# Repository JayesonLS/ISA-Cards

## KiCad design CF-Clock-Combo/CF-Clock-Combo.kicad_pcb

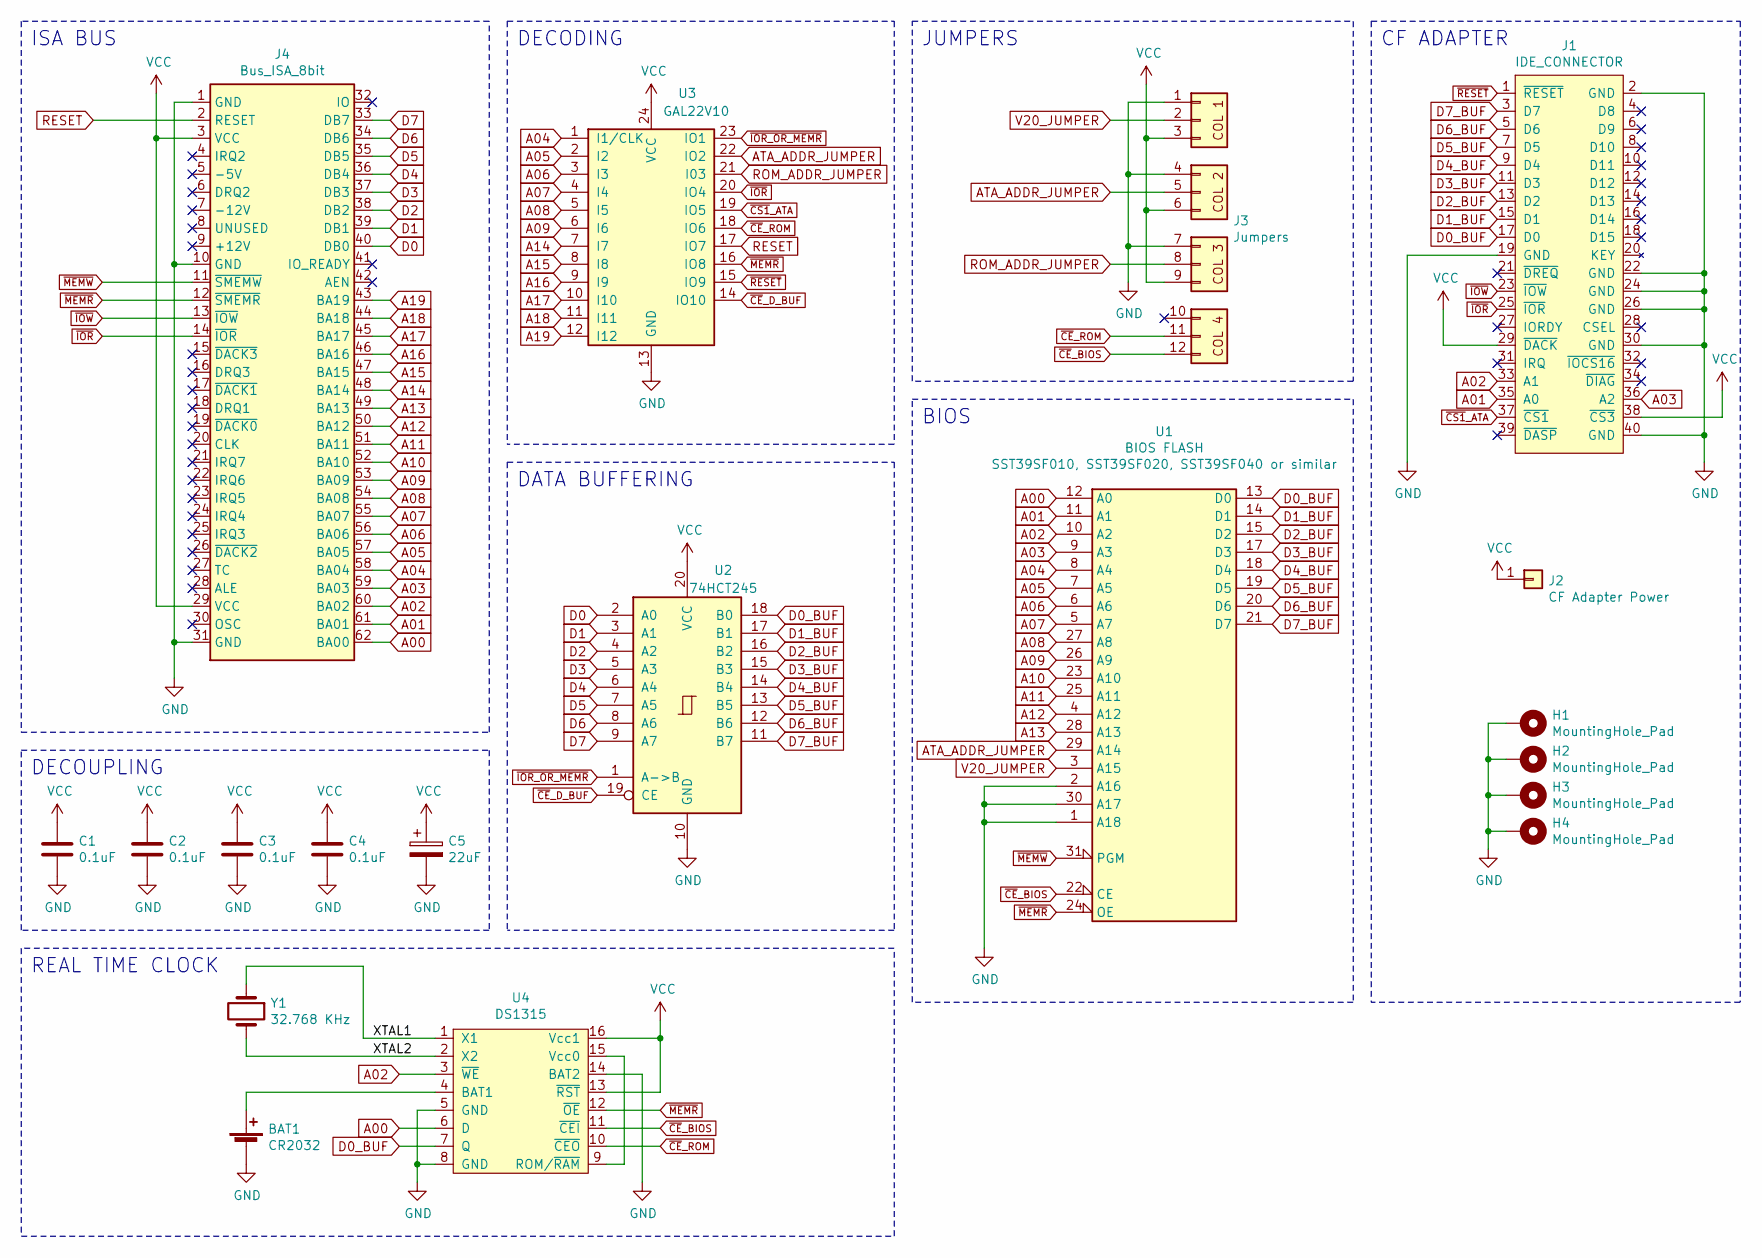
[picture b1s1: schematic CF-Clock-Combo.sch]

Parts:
BAT1: CR2032; BatteryHolder_Keystone_103_1x20mm
C1, C2, C3, C4: 0.1uF; C_Disc_D6.0mm_W2.5mm_P5.00mm
C5: 22uF; CP_Radial_D5.0mm_P2.50mm
H1, H2, H3, H4: MountingHole_Pad; MountingHole_3.5mm_Pad
J1: IDE_CONNECTOR; PinSocket_2x20_P2.54mm_Vertical
J2: CF Adapter Power; PinSocket_1x01_P2.54mm_Vertical
J3: Jumpers; PinHeader_3x04_P2.54mm_Vertical
J4: Bus_ISA_8bit; BUS_XT
U1: BIOS FLASH; DIP-32_W15.24mm_Socket
U2: 74HCT245; DIP-20_W7.62mm_Socket
U3: GAL22V10; DIP-24_W7.62mm_Socket
U4: DS1315; DIP-16_W7.62mm_Socket
Y1: 32.768 KHz; Crystal_C38-LF_D3.0mm_L8.0mm_Horizontal

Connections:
/XTAL1: U4.1 (X1), Y1.1
/XTAL2: U4.2 (X2), Y1.2
A00: J4.62 (BA00), U1.12 (A0), U4.6 (D)
A01: J1.35 (A0), J4.61 (BA01), U1.11 (A1)
A02: J1.33 (A1), J4.60 (BA02), U1.10 (A2), U4.3 (~WE)
A03: J1.36 (A2), J4.59 (BA03), U1.9 (A3)
A04: J4.58 (BA04), U1.8 (A4), U3.1 (I1/CLK)
A05: J4.57 (BA05), U1.7 (A5), U3.2 (I2)
A06: J4.56 (BA06), U1.6 (A6), U3.3 (I3)
A07: J4.55 (BA07), U1.5 (A7), U3.4 (I4)
A08: J4.54 (BA08), U1.27 (A8), U3.5 (I5)
A09: J4.53 (BA09), U1.26 (A9), U3.6 (I6)
A10: J4.52 (BA10), U1.23 (A10)
A11: J4.51 (BA11), U1.25 (A11)
A12: J4.50 (BA12), U1.4 (A12)
A13: J4.49 (BA13), U1.28 (A13)
A14: J4.48 (BA14), U3.7 (I7)
A15: J4.47 (BA15), U3.8 (I8)
A16: J4.46 (BA16), U3.9 (I9)
A17: J4.45 (BA17), U3.10 (I10)
A18: J4.44 (BA18), U3.11 (I11)
A19: J4.43 (BA19), U3.12 (I12)
ATA_ADDR_JUMPER: J3.5, U1.29 (A14), U3.22 (IO2)
D0: J4.40 (DB0), U2.2 (A0)
D0_BUF: J1.17 (D0), U1.13 (D0), U2.18 (B0), U4.7 (Q)
D1: J4.39 (DB1), U2.3 (A1)
D1_BUF: J1.15 (D1), U1.14 (D1), U2.17 (B1)
D2: J4.38 (DB2), U2.4 (A2)
D2_BUF: J1.13 (D2), U1.15 (D2), U2.16 (B2)
D3: J4.37 (DB3), U2.5 (A3)
D3_BUF: J1.11 (D3), U1.17 (D3), U2.15 (B3)
D4: J4.36 (DB4), U2.6 (A4)
D4_BUF: J1.9 (D4), U1.18 (D4), U2.14 (B4)
D5: J4.35 (DB5), U2.7 (A5)
D5_BUF: J1.7 (D5), U1.19 (D5), U2.13 (B5)
D6: J4.34 (DB6), U2.8 (A6)
D6_BUF: J1.5 (D6), U1.20 (D6), U2.12 (B6)
D7: J4.33 (DB7), U2.9 (A7)
D7_BUF: J1.3 (D7), U1.21 (D7), U2.11 (B7)
GND: BAT1.2 (-), C1.2, C2.2, C3.2, C4.2, C5.2, H1.1, H2.1, H3.1, H4.1, J1.2 (GND), J1.19 (GND), J1.22 (GND), J1.24 (GND), J1.26 (GND), J1.30 (GND), J1.40 (GND), J3.1, J3.4, J3.7, J4.1 (GND), J4.10 (GND), J4.31 (GND), U1.1 (A18), U1.2 (A16), U1.16 (GND), U1.30 (A17), U2.10 (GND), U3.13 (GND), U4.5 (GND), U4.8 (GND), U4.14 (BAT2)
unnamed: BAT1.1 (+), U4.4 (BAT1)
unnamed: U4.9 (ROM/~RAM), U4.15 (Vcc0)
RESET: J4.2 (RESET), U3.17 (IO7)
ROM_ADDR_JUMPER: J3.8, U3.21 (I03)
V20_JUMPER: J3.2, U1.3 (A15)
VCC: C1.1, C2.1, C3.1, C4.1, C5.1, J1.29 (~DACK), J1.38 (~CS3), J2.1, J3.3 (Pin_4), J3.6, J3.9, J4.3 (VCC), J4.29 (VCC), U1.32 (VCC), U2.20 (VCC), U3.24 (VCC), U4.13 (~RST), U4.16 (Vcc1)
~CE~_BIOS: J3.12, U1.22 (CE), U4.11 (~CEI)
~CE~_D_BUF: U2.19 (CE), U3.14 (IO10)
~CE~_ROM: J3.11, U3.18 (IO6), U4.10 (~CEO)
~CS1~_ATA: J1.37 (~CS1), U3.19 (IO5)
~IOR: J1.25 (~IOR), J4.14 (~IOR), U3.20 (IO4)
~IOR_OR_MEMR: U2.1 (A->B), U3.23 (IO1)
~IOW: J1.23 (~IOW), J4.13 (~IOW)
~MEMR: J4.12 (~SMEMR), U1.24 (OE), U3.16 (IO8), U4.12 (~OE)
~MEMW: J4.11 (~SMEMW), U1.31 (PGM)
~RESET: J1.1 (~RESET), U3.15 (IO9)

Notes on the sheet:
ISA BUS
DECOUPLING
DATA BUFFERING
DECODING
BIOS
CF ADAPTER
JUMPERS
REAL TIME CLOCK

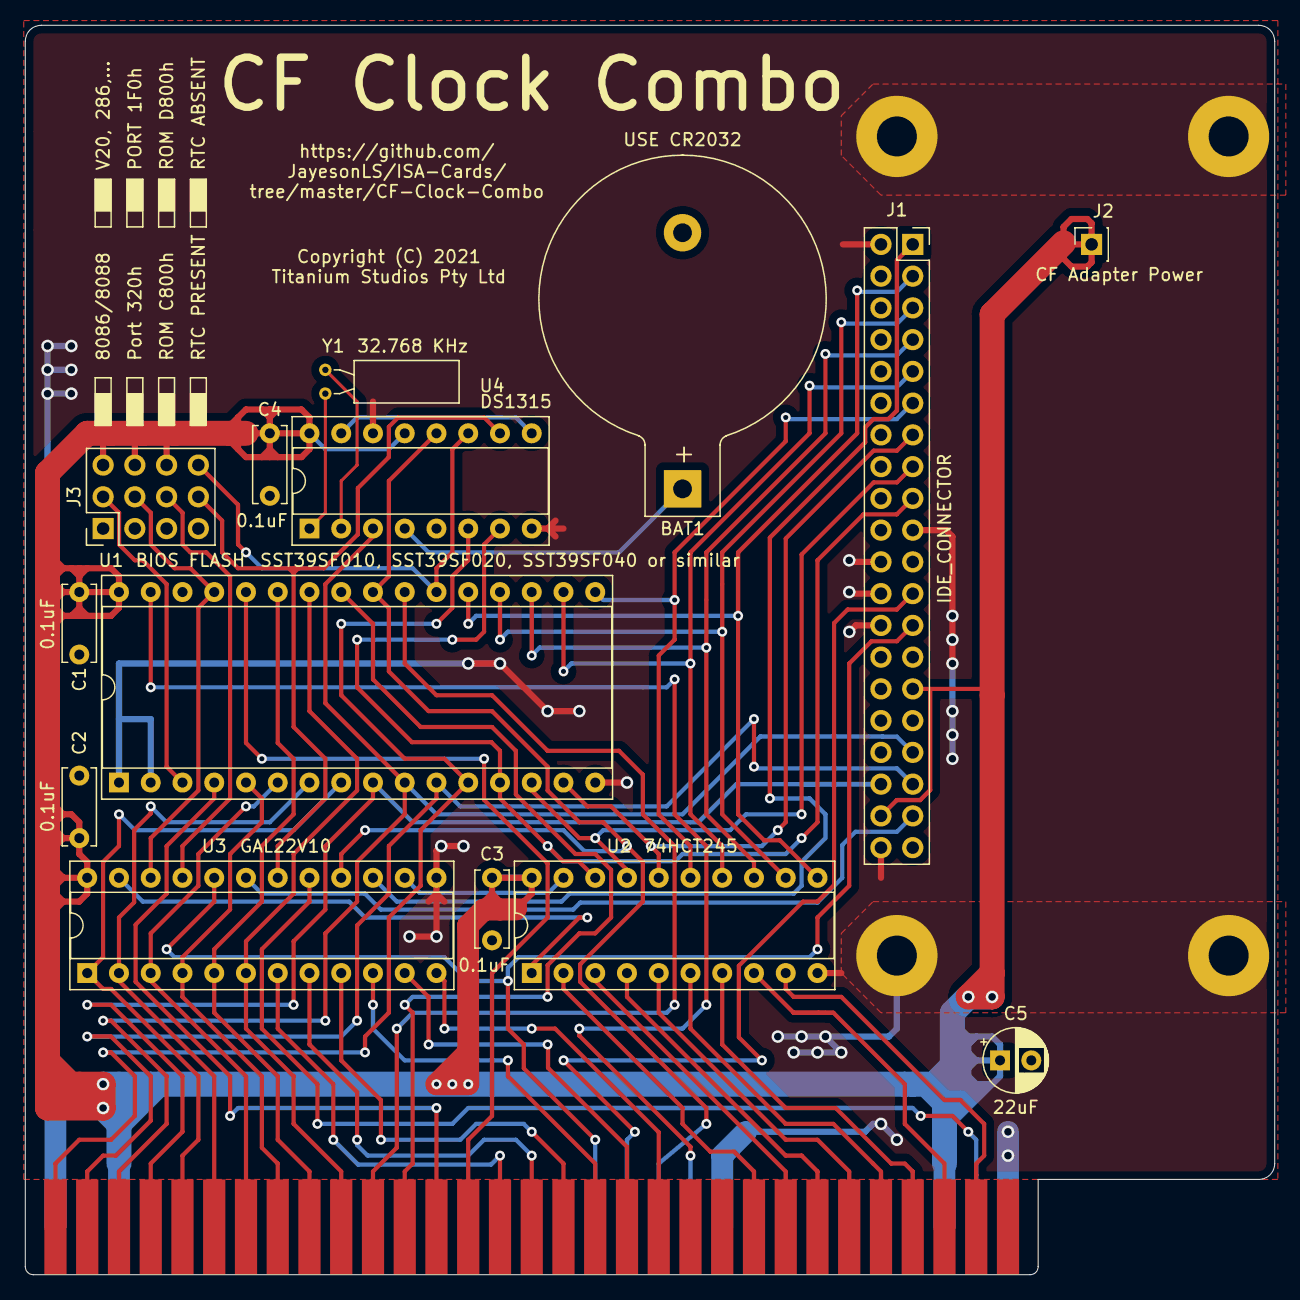
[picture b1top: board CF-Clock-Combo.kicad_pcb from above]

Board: 2 copper layers, 99.9 x 99.9 mm, 19 parts (0 on the bottom side), 56 nets.

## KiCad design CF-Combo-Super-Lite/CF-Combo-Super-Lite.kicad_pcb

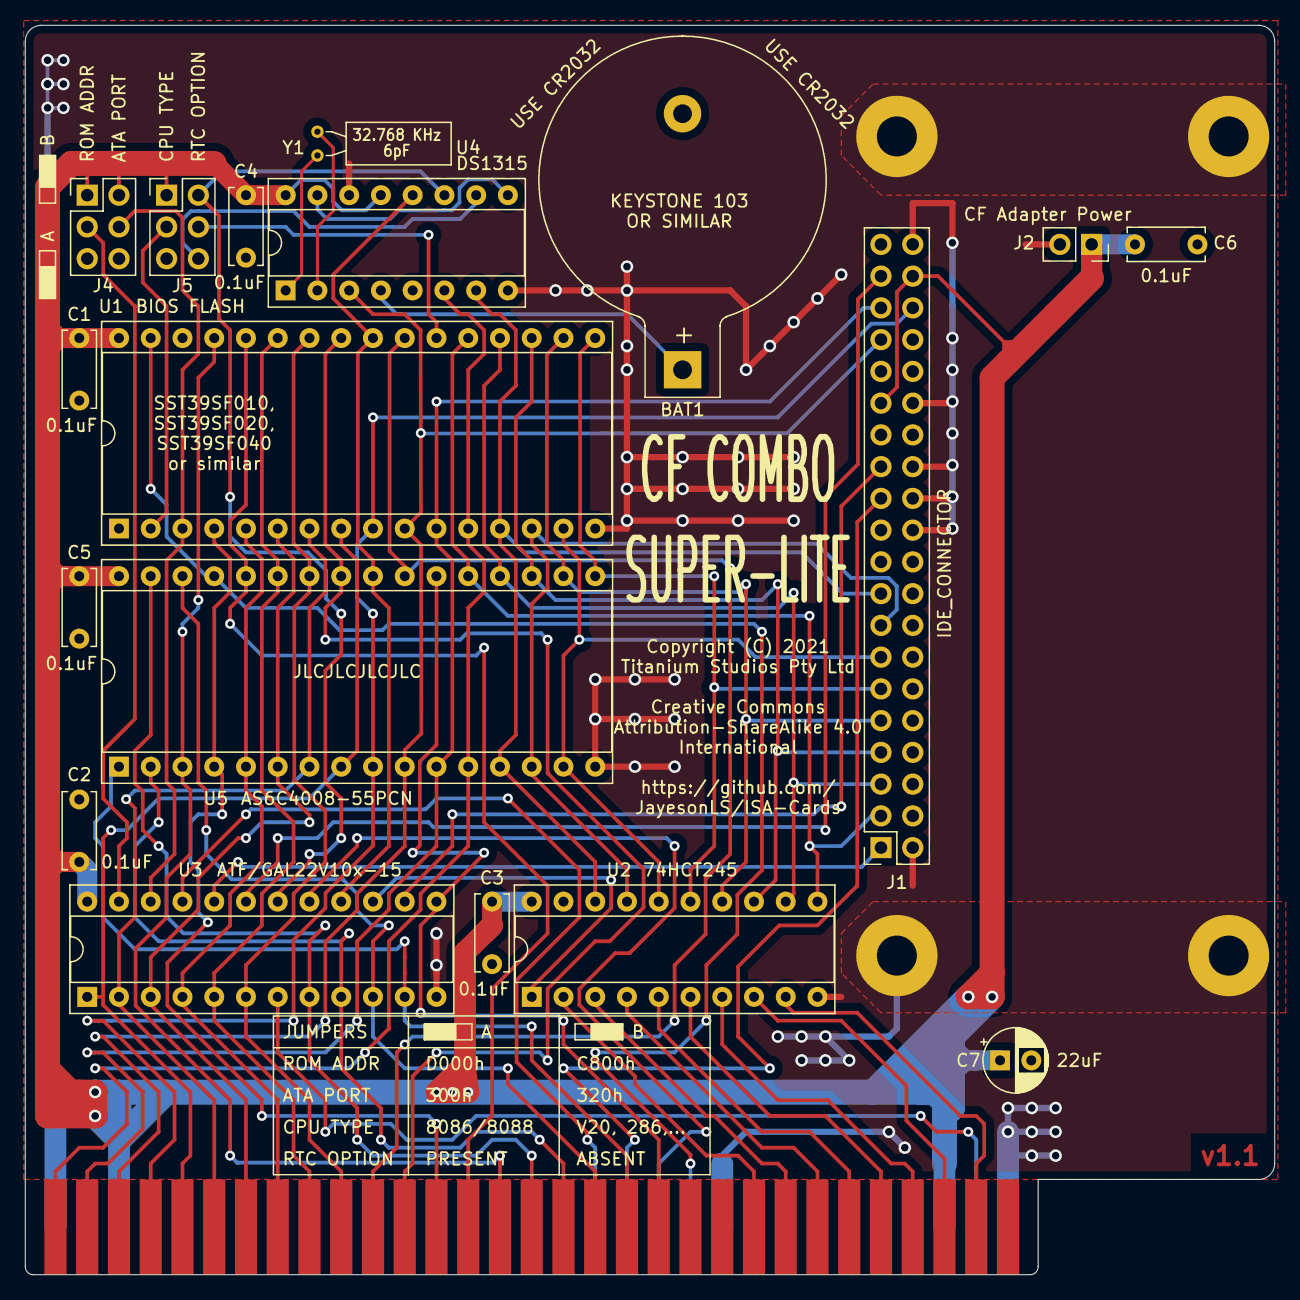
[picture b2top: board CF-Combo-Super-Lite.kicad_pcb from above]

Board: 2 copper layers, 99.9 x 99.9 mm, 23 parts (0 on the bottom side), 58 nets.

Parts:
BAT1: CR2032; BatteryHolder_Keystone_103_1x20mm
C1, C2, C3, C4, C5, C6: 0.1uF; C_Disc_D6.0mm_W2.5mm_P5.00mm
C7: 22uF; CP_Radial_D5.0mm_P2.50mm
H1, H2, H3, H4: MountingHole_Pad; MountingHole_3.5mm_Pad
J1: IDE_CONNECTOR; PinSocket_2x20_P2.54mm_Vertical
J2: CF Adapter Power; PinSocket_1x02_P2.54mm_Vertical
J3: Bus_ISA_8bit; BUS_XT
J4, J5: Addresses; PinHeader_2x03_P2.54mm_Vertical
U1: BIOS FLASH; DIP-32_W15.24mm_Socket
U2: 74HCT245; DIP-20_W7.62mm_Socket
U3: ATF/GAL22V10x-15; DIP-24_W7.62mm_Socket
U4: DS1315; DIP-16_W7.62mm_Socket
U5: AS6C4008-55PCN; DIP-32_W15.24mm_Socket
Y1: 32.768 KHz; Crystal_C38-LF_D3.0mm_L8.0mm_Horizontal

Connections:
/XTAL1: U4.1, Y1.1
/XTAL2: U4.2, Y1.2
A00: J3.62, U1.12, U4.6, U5.12
A01: J1.35, J3.61, U1.11, U5.11
A02: J1.33, J3.60, U1.10, U4.3, U5.10
A03: J1.36, J3.59, U1.9, U5.9
A04: J3.58, U1.8, U3.1, U5.8
A05: J3.57, U1.7, U3.2, U5.7
A06: J3.56, U1.6, U3.3, U5.6
A07: J3.55, U1.5, U3.4, U5.5
A08: J3.54, U1.27, U3.5, U5.27
A09: J3.53, U1.26, U3.6, U5.26
A10: J3.52, U1.23, U5.23
A11: J3.51, U1.25, U5.25
A12: J3.50, U1.4, U5.4
A13: J3.49, U1.28, U5.28
A14: J3.48, U1.29, U5.3
A15: J3.47, U3.8, U5.31
A16: J3.46, U3.9, U5.2
A17: J3.45, U3.10, U5.30
A18: J3.44, U3.11, U5.1
A19: J3.43, U3.13, U5.22
ATA_ADDR_JUMPER: J4.4, U1.3, U3.22
D0: J3.40, U2.2
D0_BUF: J1.17, U1.13, U2.18, U4.7, U5.13
D1: J3.39, U2.3
D1_BUF: J1.15, U1.14, U2.17, U5.14
D2: J3.38, U2.4
D2_BUF: J1.13, U1.15, U2.16, U5.15
D3: J3.37, U2.5
D3_BUF: J1.11, U1.17, U2.15, U5.17
D4: J3.36, U2.6
D4_BUF: J1.9, U1.18, U2.14, U5.18
D5: J3.35, U2.7
D5_BUF: J1.7, U1.19, U2.13, U5.19
D6: J3.34, U2.8
D6_BUF: J1.5, U1.20, U2.12, U5.20
D7: J3.33, U2.9
D7_BUF: J1.3, U1.21, U2.11, U5.21
GND: BAT1.2, C1.2, C2.2, C3.2, C4.2, C5.2, C6.2, C7.2, H1.1, H2.1, H3.1, H4.1, J1.2, J1.19, J1.22, J1.24, J1.26, J1.30, J1.40, J2.2, J3.1, J3.10, J3.31, J4.5, J4.6, J5.5, U1.1, U1.16, U1.30, U2.10, U2.19, U3.12, U4.5, U4.8, U4.14, U5.16
unnamed: BAT1.1, U4.4
unnamed: U4.9, U4.15
RESET: J3.2, U3.7
ROM_ADDR_JUMPER: J4.3, U3.23
V20_JUMPER: J5.3, U1.2
VCC: C1.1, C2.1, C3.1, C4.1, C5.1, C6.1, C7.1, J1.29, J1.38, J2.1, J3.3, J3.29, J4.1, J4.2, J5.1, U1.32, U2.20, U3.24, U4.13, U4.16, U5.32
~CE~_BIOS: J5.4, U1.22
~CE~_BIOS_DECODE: J5.2, U3.18, U4.11
~CE~_BIOS_THRU: J5.6, U4.10
~CS1~_ATA: J1.37, U3.19
~IOR: J3.14, U3.21
~IOR_OR_MEMR: U2.1, U3.15
~IOR~_DELAYED: J1.25, U3.14
~IOW: J1.23, J3.13
~MEMR: J3.12, U3.17
~MEMR~_DELAYED: U1.24, U3.16, U4.12, U5.24
~MEMW: J3.11, U1.31, U5.29
~RESET: J1.1, U3.20

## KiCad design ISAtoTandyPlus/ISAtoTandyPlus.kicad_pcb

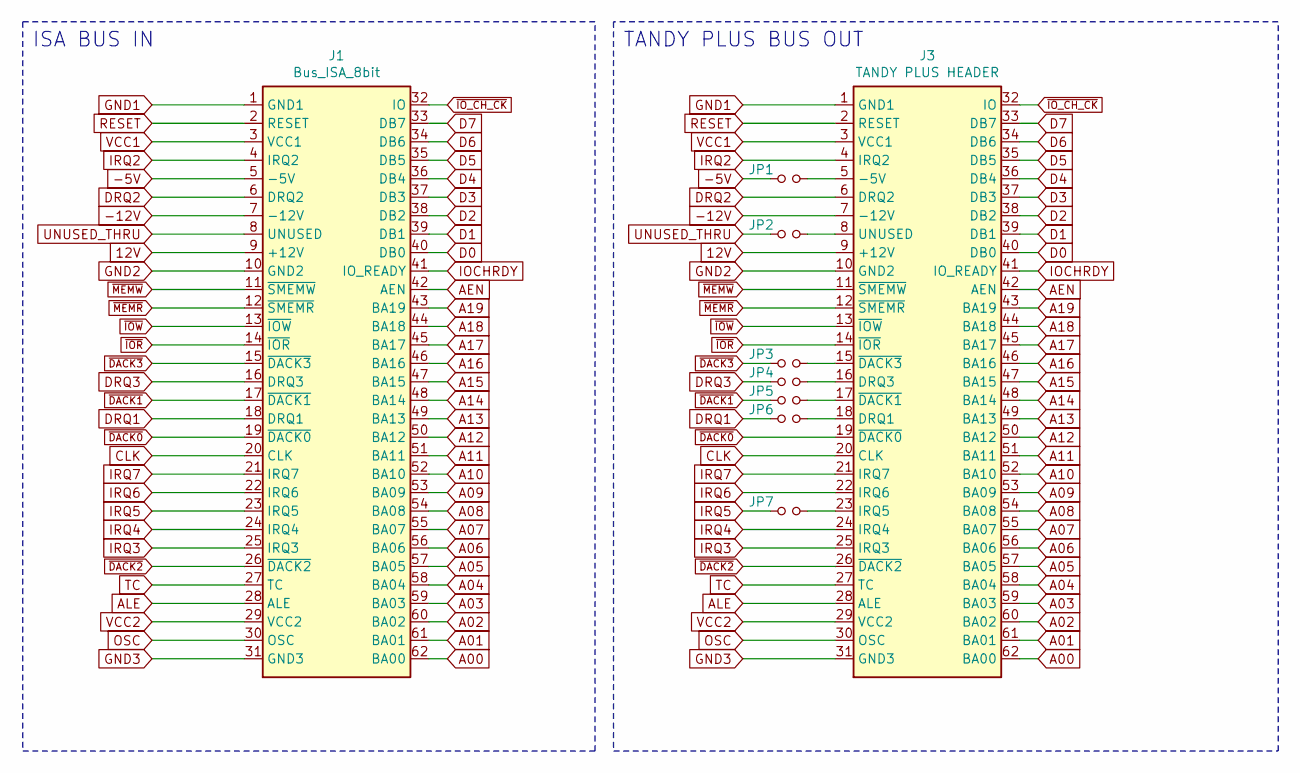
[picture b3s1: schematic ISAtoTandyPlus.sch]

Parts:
J1: Bus_ISA_8bit; BUS_XT
J3: TANDY PLUS HEADER; PinHeader_2x31_P2.54mm_Vertical
JP1: -5V; SolderJumper-2_P1.3mm_Open_RoundedPad1.0x1.5mm
JP2: AUDIO_IN; SolderJumper-2_P1.3mm_Open_RoundedPad1.0x1.5mm
JP3: ~DACK3; SolderJumper-2_P1.3mm_Open_RoundedPad1.0x1.5mm
JP4: DRQ3; SolderJumper-2_P1.3mm_Open_RoundedPad1.0x1.5mm
JP5: ~DACK1; SolderJumper-2_P1.3mm_Open_RoundedPad1.0x1.5mm
JP6: DRQ1; SolderJumper-2_P1.3mm_Open_RoundedPad1.0x1.5mm
JP7: IRQ5; SolderJumper-2_P1.3mm_Open_RoundedPad1.0x1.5mm

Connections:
12V: J1.9 (+12V), J3.9 (+12V)
-5V: J1.5 (-5V), JP1.1
-12V: J1.7 (-12V), J3.7 (-12V)
A00: J1.62 (BA00), J3.62 (BA00)
A01: J1.61 (BA01), J3.61 (BA01)
A02: J1.60 (BA02), J3.60 (BA02)
A03: J1.59 (BA03), J3.59 (BA03)
A04: J1.58 (BA04), J3.58 (BA04)
A05: J1.57 (BA05), J3.57 (BA05)
A06: J1.56 (BA06), J3.56 (BA06)
A07: J1.55 (BA07), J3.55 (BA07)
A08: J1.54 (BA08), J3.54 (BA08)
A09: J1.53 (BA09), J3.53 (BA09)
A10: J1.52 (BA10), J3.52 (BA10)
A11: J1.51 (BA11), J3.51 (BA11)
A12: J1.50 (BA12), J3.50 (BA12)
A13: J1.49 (BA13), J3.49 (BA13)
A14: J1.48 (BA14), J3.48 (BA14)
A15: J1.47 (BA15), J3.47 (BA15)
A16: J1.46 (BA16), J3.46 (BA16)
A17: J1.45 (BA17), J3.45 (BA17)
A18: J1.44 (BA18), J3.44 (BA18)
A19: J1.43 (BA19), J3.43 (BA19)
AEN: J1.42 (AEN), J3.42 (AEN)
ALE: J1.28 (ALE), J3.28 (ALE)
CLK: J1.20 (CLK), J3.20 (CLK)
D0: J1.40 (DB0), J3.40 (DB0)
D1: J1.39 (DB1), J3.39 (DB1)
D2: J1.38 (DB2), J3.38 (DB2)
D3: J1.37 (DB3), J3.37 (DB3)
D4: J1.36 (DB4), J3.36 (DB4)
D5: J1.35 (DB5), J3.35 (DB5)
D6: J1.34 (DB6), J3.34 (DB6)
D7: J1.33 (DB7), J3.33 (DB7)
DRQ1: J1.18 (DRQ1), JP6.1
DRQ2: J1.6 (DRQ2), J3.6 (DRQ2)
DRQ3: J1.16 (DRQ3), JP4.1
GND1: J1.1 (GND1), J3.1 (GND1)
GND2: J1.10 (GND2), J3.10 (GND2)
GND3: J1.31 (GND3), J3.31 (GND3)
IOCHRDY: J1.41 (IO_READY), J3.41 (IO_READY)
IRQ2: J1.4 (IRQ2), J3.4 (IRQ2)
IRQ3: J1.25 (IRQ3), J3.25 (IRQ3)
IRQ4: J1.24 (IRQ4), J3.24 (IRQ4)
IRQ5: J1.23 (IRQ5), JP7.1
IRQ6: J1.22 (IRQ6), J3.22 (IRQ6)
IRQ7: J1.21 (IRQ7), J3.21 (IRQ7)
unnamed: J3.5 (-5V), JP1.2
unnamed: J3.8 (UNUSED), JP2.2
unnamed: J3.15 (~DACK3), JP3.2
unnamed: J3.16 (DRQ3), JP4.2
unnamed: J3.17 (~DACK1), JP5.2
unnamed: J3.18 (DRQ1), JP6.2
unnamed: J3.23 (IRQ5), JP7.2
OSC: J1.30 (OSC), J3.30 (OSC)
RESET: J1.2 (RESET), J3.2 (RESET)
TC: J1.27 (TC), J3.27 (TC)
UNUSED_THRU: J1.8 (UNUSED), JP2.1
VCC1: J1.3 (VCC1), J3.3 (VCC1)
VCC2: J1.29 (VCC2), J3.29 (VCC2)
~DACK0: J1.19 (~DACK0), J3.19 (~DACK0)
~DACK1: J1.17 (~DACK1), JP5.1
~DACK2: J1.26 (~DACK2), J3.26 (~DACK2)
~DACK3: J1.15 (~DACK3), JP3.1
~IOR: J1.14 (~IOR), J3.14 (~IOR)
~IOW: J1.13 (~IOW), J3.13 (~IOW)
~IO_CH_CK: J1.32 (IO), J3.32 (IO)
~MEMR: J1.12 (~SMEMR), J3.12 (~SMEMR)
~MEMW: J1.11 (~SMEMW), J3.11 (~SMEMW)

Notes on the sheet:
ISA BUS IN
TANDY PLUS BUS OUT

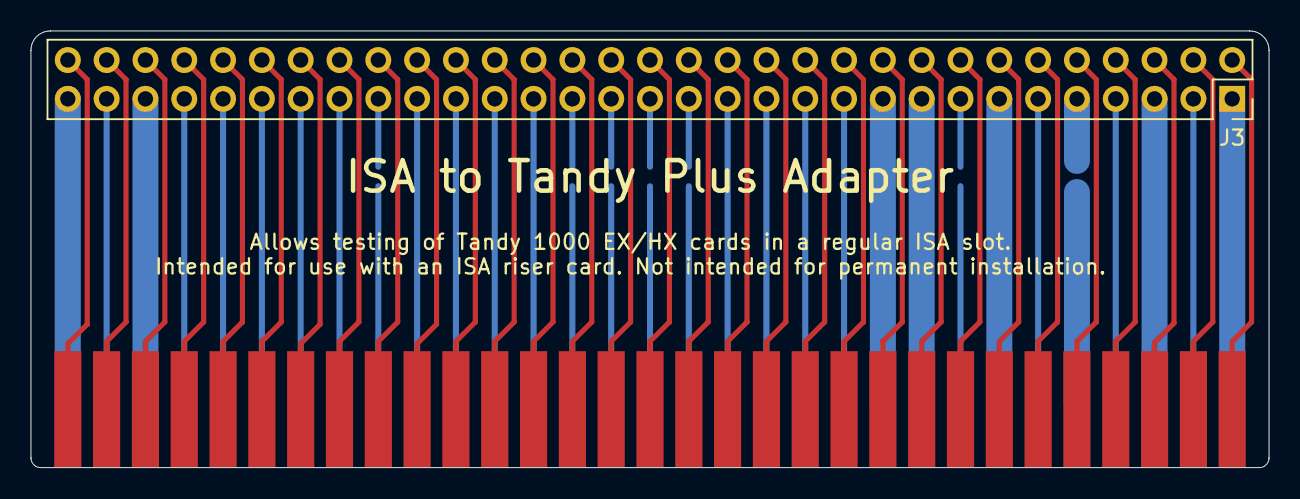
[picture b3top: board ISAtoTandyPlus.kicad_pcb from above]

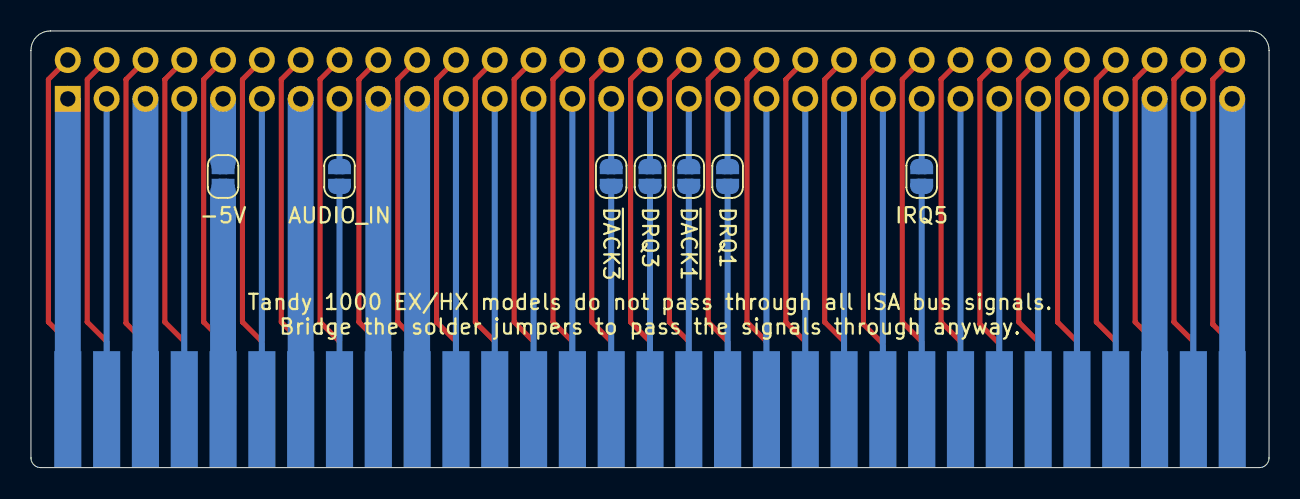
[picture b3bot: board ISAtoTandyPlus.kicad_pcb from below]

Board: 2 copper layers, 81.0 x 28.6 mm, 9 parts (7 on the bottom side), 69 nets.

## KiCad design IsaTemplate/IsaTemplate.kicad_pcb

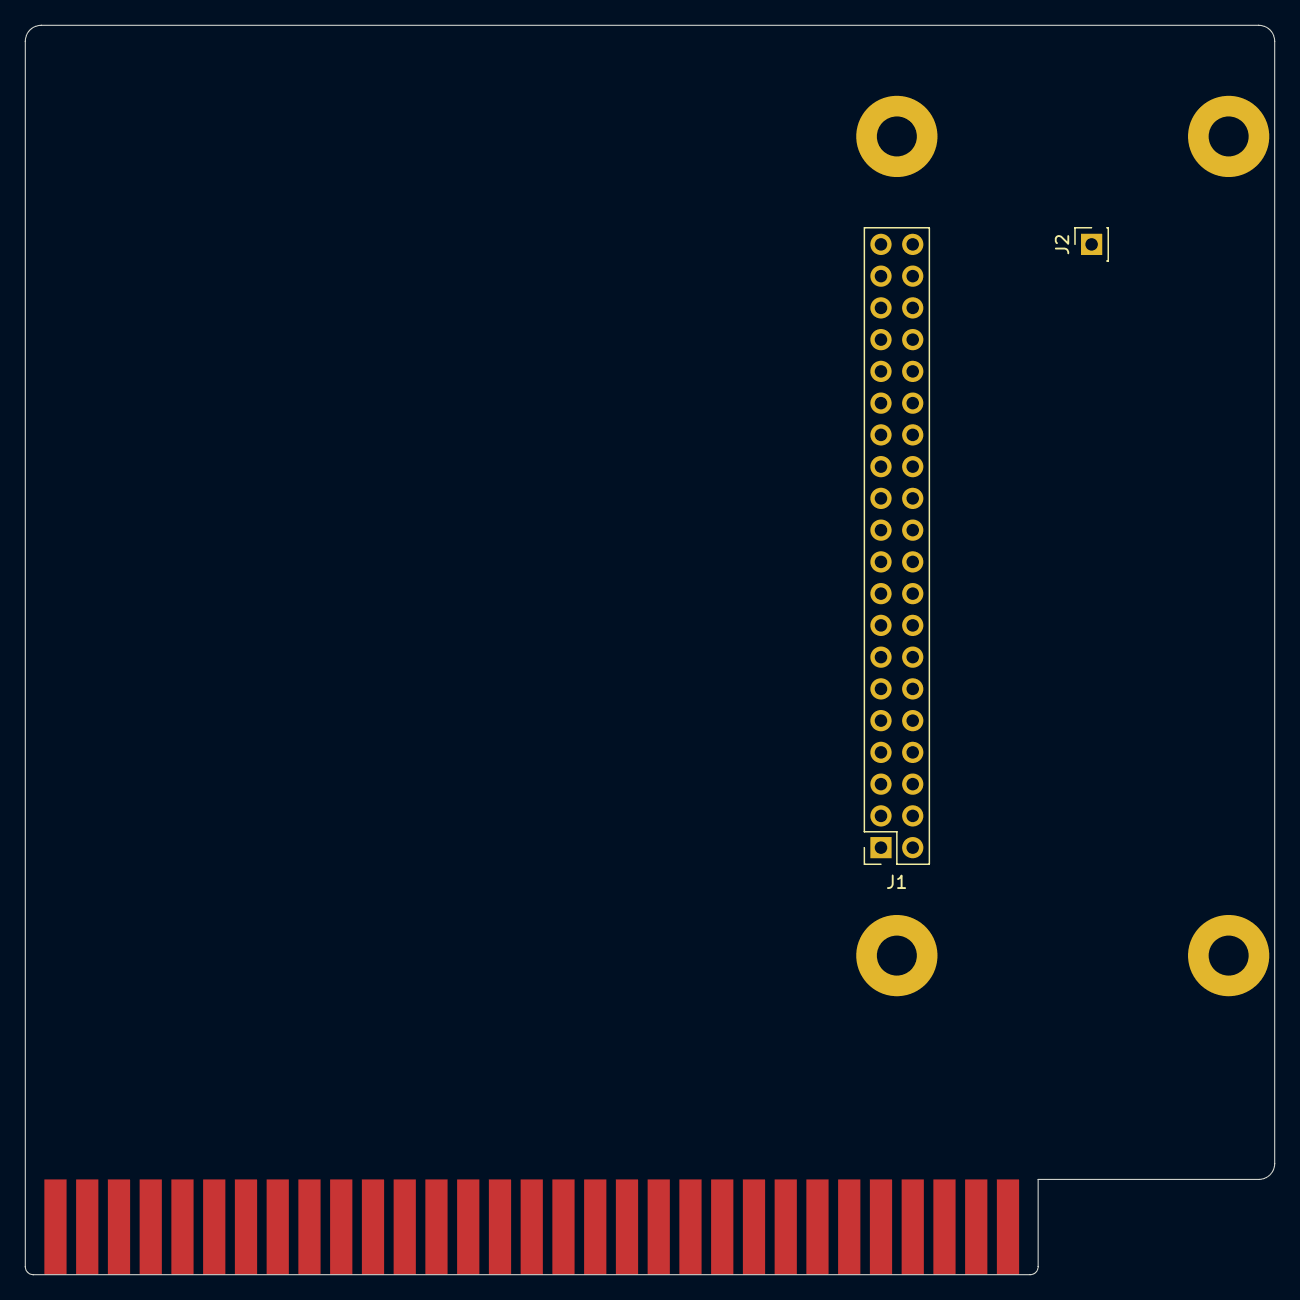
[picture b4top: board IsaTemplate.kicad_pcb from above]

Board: 2 copper layers, 99.9 x 99.9 mm, 7 parts (0 on the bottom side), 2 nets, no tracks yet.

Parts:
H1, H2, H3, H4: MountingHole_Pad; MountingHole_3.5mm_Pad
J1: IDE_CONNECTOR; PinSocket_2x20_P2.54mm_Vertical
J2: CF Adapter Power; PinSocket_1x01_P2.54mm_Vertical
J3: Bus_ISA_8bit; BUS_XT

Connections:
GND: J3.1, J3.10, J3.31
VCC: J2.1, J3.3, J3.29

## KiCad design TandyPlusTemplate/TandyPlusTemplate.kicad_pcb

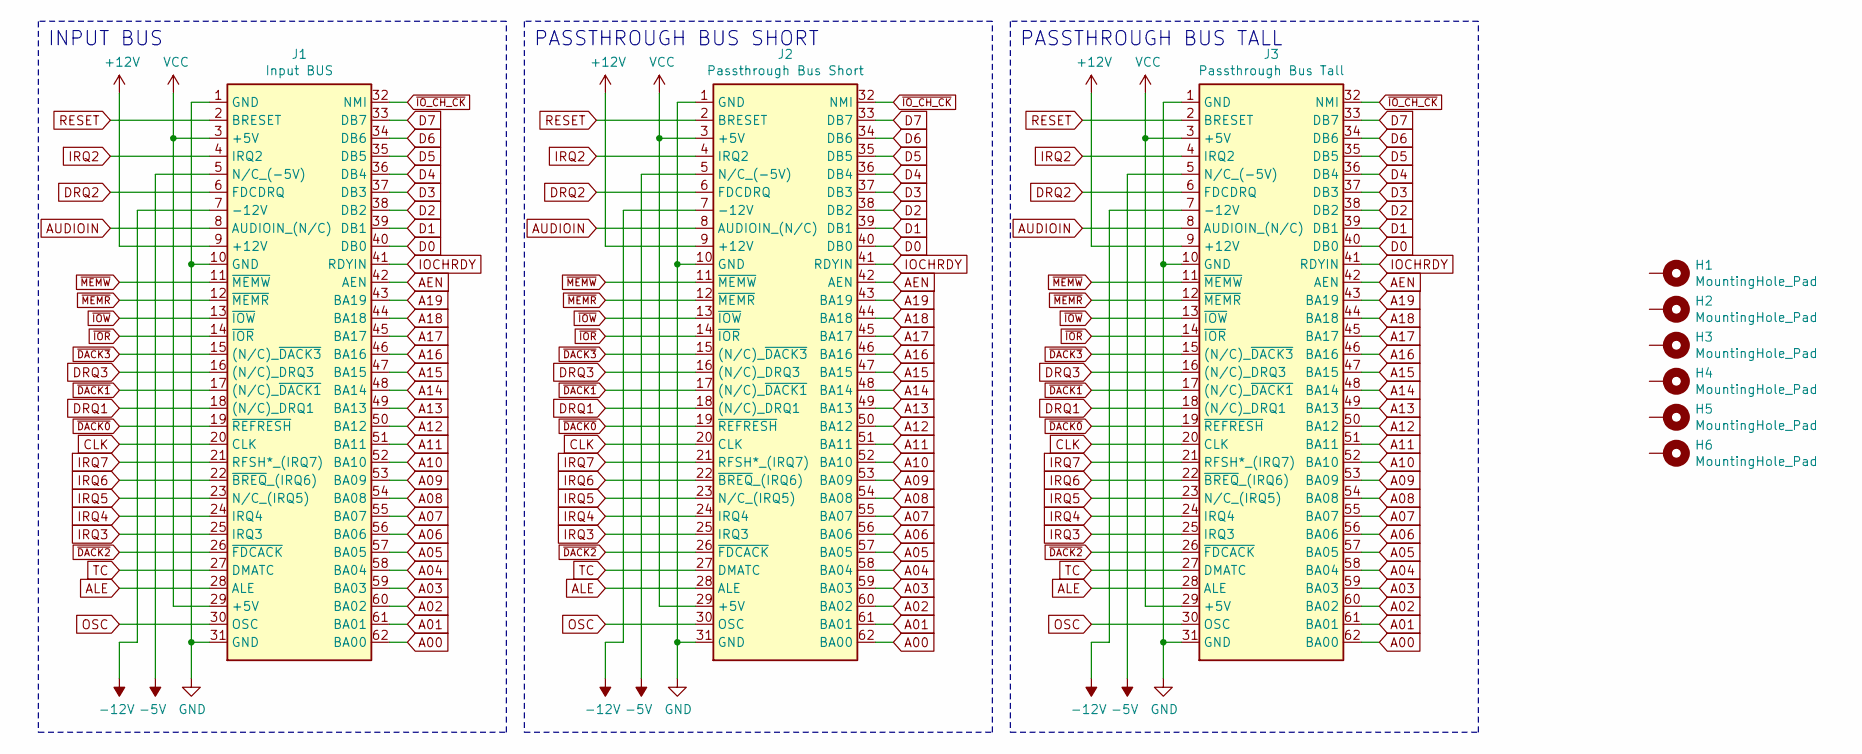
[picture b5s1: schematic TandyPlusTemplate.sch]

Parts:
H1, H2, H3, H4, H5, H6: MountingHole_Pad; MountingHole_3.5mm_Pad
J1: Input BUS; TandyPlusSocket
J2: Passthrough Bus Short; TandyPlusShortPins
J3: Passthrough Bus Tall; TandyPlusLongPins

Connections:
+12V: J1.9 (+12V), J2.9 (+12V), J3.9 (+12V)
-5V: J1.5 (N/C_(-5V)), J2.5 (N/C_(-5V)), J3.5 (N/C_(-5V))
-12V: J1.7 (-12V), J2.7 (-12V), J3.7 (-12V)
A00: J1.62 (BA00), J2.62 (BA00), J3.62 (BA00)
A01: J1.61 (BA01), J2.61 (BA01), J3.61 (BA01)
A02: J1.60 (BA02), J2.60 (BA02), J3.60 (BA02)
A03: J1.59 (BA03), J2.59 (BA03), J3.59 (BA03)
A04: J1.58 (BA04), J2.58 (BA04), J3.58 (BA04)
A05: J1.57 (BA05), J2.57 (BA05), J3.57 (BA05)
A06: J1.56 (BA06), J2.56 (BA06), J3.56 (BA06)
A07: J1.55 (BA07), J2.55 (BA07), J3.55 (BA07)
A08: J1.54 (BA08), J2.54 (BA08), J3.54 (BA08)
A09: J1.53 (BA09), J2.53 (BA09), J3.53 (BA09)
A10: J1.52 (BA10), J2.52 (BA10), J3.52 (BA10)
A11: J1.51 (BA11), J2.51 (BA11), J3.51 (BA11)
A12: J1.50 (BA12), J2.50 (BA12), J3.50 (BA12)
A13: J1.49 (BA13), J2.49 (BA13), J3.49 (BA13)
A14: J1.48 (BA14), J2.48 (BA14), J3.48 (BA14)
A15: J1.47 (BA15), J2.47 (BA15), J3.47 (BA15)
A16: J1.46 (BA16), J2.46 (BA16), J3.46 (BA16)
A17: J1.45 (BA17), J2.45 (BA17), J3.45 (BA17)
A18: J1.44 (BA18), J2.44 (BA18), J3.44 (BA18)
A19: J1.43 (BA19), J2.43 (BA19), J3.43 (BA19)
AEN: J1.42 (AEN), J2.42 (AEN), J3.42 (AEN)
ALE: J1.28 (ALE), J2.28 (ALE), J3.28 (ALE)
AUDIOIN: J1.8 (AUDIOIN_(N/C)), J2.8 (AUDIOIN_(N/C)), J3.8 (AUDIOIN_(N/C))
CLK: J1.20 (CLK), J2.20 (CLK), J3.20 (CLK)
D0: J1.40 (DB0), J2.40 (DB0), J3.40 (DB0)
D1: J1.39 (DB1), J2.39 (DB1), J3.39 (DB1)
D2: J1.38 (DB2), J2.38 (DB2), J3.38 (DB2)
D3: J1.37 (DB3), J2.37 (DB3), J3.37 (DB3)
D4: J1.36 (DB4), J2.36 (DB4), J3.36 (DB4)
D5: J1.35 (DB5), J2.35 (DB5), J3.35 (DB5)
D6: J1.34 (DB6), J2.34 (DB6), J3.34 (DB6)
D7: J1.33 (DB7), J2.33 (DB7), J3.33 (DB7)
DRQ1: J1.18 ((N/C)_DRQ1), J2.18 ((N/C)_DRQ1), J3.18 ((N/C)_DRQ1)
DRQ2: J1.6 (FDCDRQ), J2.6 (FDCDRQ), J3.6 (FDCDRQ)
DRQ3: J1.16 ((N/C)_DRQ3), J2.16 ((N/C)_DRQ3), J3.16 ((N/C)_DRQ3)
GND: J1.1 (GND), J1.10 (GND), J1.31 (GND), J2.1 (GND), J2.10 (GND), J2.31 (GND), J3.1 (GND), J3.10 (GND), J3.31 (GND)
IOCHRDY: J1.41 (RDYIN), J2.41 (RDYIN), J3.41 (RDYIN)
IRQ2: J1.4 (IRQ2), J2.4 (IRQ2), J3.4 (IRQ2)
IRQ3: J1.25 (IRQ3), J2.25 (IRQ3), J3.25 (IRQ3)
IRQ4: J1.24 (IRQ4), J2.24 (IRQ4), J3.24 (IRQ4)
IRQ5: J1.23 (N/C_(IRQ5)), J2.23 (N/C_(IRQ5)), J3.23 (N/C_(IRQ5))
IRQ6: J1.22 (~BREQ~_(IRQ6)), J2.22 (~BREQ~_(IRQ6)), J3.22 (~BREQ~_(IRQ6))
IRQ7: J1.21 (RFSH*_(IRQ7)), J2.21 (RFSH*_(IRQ7)), J3.21 (RFSH*_(IRQ7))
OSC: J1.30 (OSC), J2.30 (OSC), J3.30 (OSC)
RESET: J1.2 (BRESET), J2.2 (BRESET), J3.2 (BRESET)
TC: J1.27 (DMATC), J2.27 (DMATC), J3.27 (DMATC)
VCC: J1.3 (+5V), J1.29 (+5V), J2.3 (+5V), J2.29 (+5V), J3.3 (+5V), J3.29 (+5V)
~DACK0: J1.19 (~REFRESH), J2.19 (~REFRESH), J3.19 (~REFRESH)
~DACK1: J1.17 ((N/C)_~DACK1), J2.17 ((N/C)_~DACK1), J3.17 ((N/C)_~DACK1)
~DACK2: J1.26 (~FDCACK), J2.26 (~FDCACK), J3.26 (~FDCACK)
~DACK3: J1.15 ((N/C)_~DACK3), J2.15 ((N/C)_~DACK3), J3.15 ((N/C)_~DACK3)
~IOR: J1.14 (~IOR), J2.14 (~IOR), J3.14 (~IOR)
~IOW: J1.13 (~IOW), J2.13 (~IOW), J3.13 (~IOW)
~IO_CH_CK: J1.32 (NMI), J2.32 (NMI), J3.32 (NMI)
~MEMR: J1.12 (~MEMR), J2.12 (~MEMR), J3.12 (~MEMR)
~MEMW: J1.11 (~MEMW), J2.11 (~MEMW), J3.11 (~MEMW)

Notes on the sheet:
INPUT BUS
PASSTHROUGH BUS SHORT
PASSTHROUGH BUS TALL

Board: 2 copper layers, 9 parts (0 on the bottom side), 59 nets, no tracks yet.

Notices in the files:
CF-Clock-Combo/CF-Clock-Combo.kicad_pcb:
Copyright (C) 2021
CF-Combo-Super-Lite/CF-Combo-Super-Lite.kicad_pcb:
Creative Commons
Attribution-ShareAlike 4.0
